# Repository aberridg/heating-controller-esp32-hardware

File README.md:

# heating-controller-esp32-hardware

This is a multi-zone heating controller, based on an ESP-32.

It uses Triacs for switching the boiler, pump and thermostats.

Right now, it is set up for 3 zones plus Domestic Hot Water.

It's designed to be used with this firmware:

https://github.com/aberridg/heating-controller-esp32-mqtt

The design can be used with physical thermostats or with triggering
via MQTT (for use with home automation systems such as Home Assistant).

[Schematic](/heating-controller-esp32.pdf)

I'm having some PCBs made/assembled by JLCPCB, so if you want one, let me know (via LinkedIn - link in my bio)! Or if you can't do that, raise an issue.

IMPORTANT: v1.0 - the connector for the thermostats is the wrong way round on the PCB, so the pin numbers are not consistent with the others. No matter, just wire accordingly. For reference, GND is the upper pin, closest to the bottom edge of the board.

Also IMPORTANT: v1.0 - to flash the ESP32, hold down the Boot button and press reset.

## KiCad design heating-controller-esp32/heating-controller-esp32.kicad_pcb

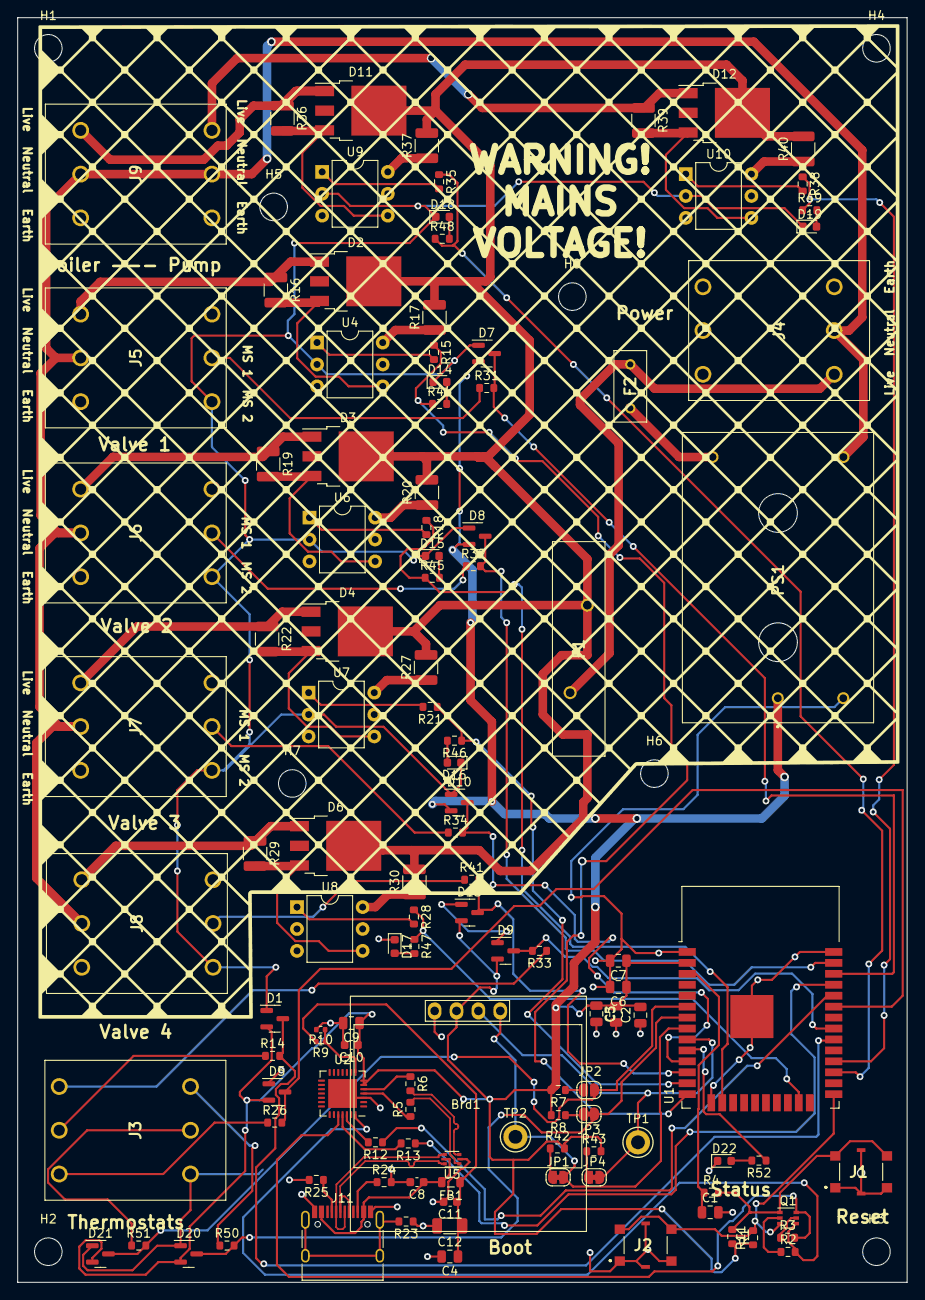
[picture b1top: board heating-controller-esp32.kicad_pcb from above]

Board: 2 copper layers, 103.3 x 146.8 mm, 125 parts (0 on the bottom side), 92 nets.

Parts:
Brd1: SSD1306; 128x64OLED
C1, C6: 1uF; C_0805_2012Metric
C2, C3, C5, C7, C9: 100nF; C_0805_2012Metric
C4: 1.0uF; C_0805_2012Metric
C8, C11: 10nF/100V; C_0603_1608Metric
C10: 4.7uF; C_0603_1608Metric
C12: 10uF; C_1206_3216Metric
D1, D5, D7, D8, D9, D10, D13, D20, D21: BAS-040; SOT-23
D2, D3, D4, D6, D11, D12: ACS2; TO-252-3_TabPin4
D14, D15, D16, D17, D18, D19, D22: RED; LED_0603_1608Metric
F1: LVR200S-240; LVR200S240
F2: MF-RM005_240-2; MFRM0052402
FB1: Ferrite_Bead; L_0805_2012Metric
H1, H2, H3, H4, H5, H6, H7, H8: MountingHole; MountingHole_3.2mm_M3_DIN965
J1, J2: 431151015826
J3, J4, J5, J6, J7, J8, J9: 76829-0104; 736303
J11: USB_C_Receptacle_USB2.0; USB_C_Receptacle_HRO_TYPE-C-31-M-12
JP1, JP4: i2cPU; SolderJumper-2_P1.3mm_Bridged_RoundedPad1.0x1.5mm
JP2: SolderJumper_2_Bridged; SolderJumper-2_P1.3mm_Open_RoundedPad1.0x1.5mm
JP3: SolderJumper_2_Bridged; SolderJumper-2_P1.3mm_Bridged_RoundedPad1.0x1.5mm
PS1: IRM-01-3.3; IRM015
Q1: MBT3904DW1; SOT-363_SC-70-6
R1: 12K; R_0603_1608Metric
R2, R3, R7, R8, R11, R42, R43: 10K; R_0603_1608Metric
R4: 22R; R_0603_1608Metric
R5, R6: 27R; R_0603_1608Metric
R9: 24K; R_0402_1005Metric
R10: 47K; R_0402_1005Metric
R12, R13: 470R; R_0603_1608Metric
R14, R26, R31, R32, R33, R34, R41, R50, R51: 4.7K; R_0603_1608Metric
R15, R18, R21, R28, R35, R38: 270R; R_0603_1608Metric
R16, R17, R19, R20, R22, R27, R29, R30, R36, R37, R39, R40: 360R; R_1210_3225Metric
R23: 1M; R_0603_1608Metric
R24, R25: 5.1K; R_0603_1608Metric
R44, R45, R46, R47, R48, R49, R52: 1K; R_0603_1608Metric
TP1, TP2: TestPoint; TestPoint_Keystone_5005-5009_Compact
U1: ESP32-WROOM-32U; ESP32-WROOM-32
U2: CP2102N-A01-GQFN28; QFN-28-1EP_5x5mm_P0.5mm_EP3.35x3.35mm
U4, U6, U7, U8, U9, U10: MOC3061M; DIP-6_W7.62mm
U5: USB ESD; SOT-666

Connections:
+3V3: Brd1.2 (VCC), C2.2, C3.1, C5.2, C6.1, C7.1, C9.1, C10.1, D1.2, D5.2, D7.2, D8.2, D9.2, D10.2, D13.2, D20.2, D21.2, PS1.1 (+V), R1.1, R7.2, R8.2, R11.1, R42.2, R43.2, U1.2 (VDD), U2.6 (VDD), U2.7 (REGIN)
/Boiler Out/Switched: D11.1 (A1), J9.1, R36.1
/Boiler Out/Trigger: R35.1, R48.1, U1.27 (IO16)
/DHW_Thermostat: J3.2, R26.1
/ESP32/DTR: Q1.4 (E2), R2.2, U2.28 (~DTR)
/ESP32/EN: C1.1, R4.1, U1.3 (EN)
/ESP32/ESP_RXD: R12.1, U1.34 (RXD0/IO3)
/ESP32/ESP_TXD: R13.1, U1.35 (TXD0/IO1)
/ESP32/GPIO_0: J2.2 (NO_1), J2.4 (NO_2), Q1.3 (C2), R11.2, U1.25 (IO0)
/ESP32/IO12: R15.1, R44.1, U1.14 (IO12)
/ESP32/IO13: R18.1, R45.1, U1.16 (IO13)
/ESP32/IO14: R21.1, R46.1, U1.13 (IO14)
/ESP32/IO15: R28.1, R47.1, U1.23 (IO15)
/ESP32/IO17: R38.1, R49.1, U1.28 (IO17)
/ESP32/IO18: D1.3, R14.2, U1.30 (IO18)
/ESP32/IO19: D9.3, R33.2, U1.31 (IO19)
/ESP32/IO21: D5.3, R26.2, U1.33 (IO21)
/ESP32/IO22: D7.3, R31.2, U1.36 (IO22)
/ESP32/IO23: D8.3, R32.2, U1.37 (IO23)
/ESP32/IO26: D10.3, R34.2, U1.11 (IO26)
/ESP32/IO27: D13.3, R41.2, U1.12 (IO27)
/ESP32/IO32: Brd1.4 (SDA), JP1.2 (B), TP2.1, U1.8 (IO32)
/ESP32/IO33: Brd1.3 (SCL), JP4.2 (B), TP1.1, U1.9 (IO33)
/ESP32/IO34: D21.3, JP2.1 (A), R51.2, U1.6 (IO34)
/ESP32/IO35: D20.3, JP3.1 (A), R50.2, U1.7 (IO35)
/ESP32/RTS: Q1.6 (C1), R3.2, U2.24 (~RTS)
/ESP32/sheet61EA3917/D+: R5.2, U5.1 (I/O1)
/ESP32/sheet61EA3917/D-: R6.2, U5.3 (I/O2)
/ESP32/sheet61EA3917/USB_D+: J11.A6 (D+), J11.B6 (D+), U5.6 (I/O1)
/ESP32/sheet61EA3917/USB_D-: J11.A7 (D-), J11.B7 (D-), U5.4 (I/O2)
/ESP32/sheet61EA3917/VBUS: C4.1, C11.1, C12.1, FB1.1, R9.1
/ESP32/~RESET: J1.2 (NO_1), J1.4 (NO_2), Q1.1 (E1), R1.2, R4.2
/Pump Out/Switched: D12.1 (A1), J9.2, R39.1
/STATUS_LED: R52.1, U1.10 (IO25)
/Spare_Thermostat: J3.4, R14.1
/Spare_Thermostat_2: J3.6, R33.1
/Spare_Thermostat_3: J3.3, R51.1
/Spare_Thermostat_4: J3.5, R50.1
/Valve Out 1/Switched: D2.1 (A1), J5.1, R16.1
/Valve Out 2/Switched: D3.1 (A1), J6.1, R19.1
/Valve Out 3/Switched: D4.1 (A1), J7.1, R22.1
/Valve Out 4/Switched: D6.1 (A1), J8.1, R29.1
/Valve_Microswitch_1: J5.4, R31.1
/Valve_Microswitch_2: J6.4, R32.1
/Valve_Microswitch_3: J7.4, R34.1
/Valve_Microswitch_4: J8.4, R41.1
Earth: J4.5, J5.5, J6.5, J7.5, J8.5, J9.5, J9.6
GND: Brd1.1 (GND), C1.2, C2.1, C3.2, C4.2, C5.1, C6.2, C7.2, C8.2, C9.2, C10.2, C11.2, C12.2, D1.1, D5.1, D7.1, D8.1, D9.1, D10.1, D13.1, D14.1 (K), D15.1 (K), D16.1 (K), D17.1 (K), D18.1 (K), D19.1 (K), D20.1, D21.1, D22.1 (K), J1.1 (COM_1), J1.3 (COM_2), J1.5 (GND_1), J1.6 (GND_2), J2.1 (COM_1), J2.3 (COM_2), J2.5 (GND_1), J2.6 (GND_2), J3.1, J5.6, J6.6, J7.6, J8.6, J11.A1 (GND), J11.A12 (GND), J11.B1 (GND), J11.B12 (GND), PS1.2 (-V), R10.2, R23.1, R24.2, R25.2, U1.1 (GND), U1.15 (GND), U1.38 (GND), U1.39 (GND), U2.3 (GND), U2.29 (GND), U4.2, U5.2 (GND), U6.2, U7.2, U8.2, U9.2, U10.2
LINE: D2.4 (A2), D3.4 (A2), D4.4 (A2), D6.4 (A2), D11.4 (A2), D12.4 (A2), F1.2, R17.2, R20.2, R27.2, R30.2, R37.2, R40.2
NEUT: J4.3, J5.3, J6.3, J7.3, J8.3, J9.3, J9.4, PS1.3 (AC/N)
unnamed: C8.1, FB1.2, J11.A4 (VBUS), J11.A9 (VBUS), J11.B4 (VBUS), J11.B9 (VBUS), U5.5 (VBUS)
unnamed: D2.3 (G), R16.2, U4.4
unnamed: D3.3 (G), R19.2, U6.4
unnamed: D4.3 (G), R22.2, U7.4
unnamed: D6.3 (G), R29.2, U8.4
unnamed: D11.3 (G), R36.2, U9.4
unnamed: D12.3 (G), R39.2, U10.4
unnamed: D14.2 (A), R44.2
unnamed: D15.2 (A), R45.2
unnamed: D16.2 (A), R46.2
unnamed: D17.2 (A), R47.2
unnamed: D18.2 (A), R48.2
unnamed: D19.2 (A), R49.2
unnamed: D22.2 (A), R52.2
unnamed: F1.1, F2.1, J4.1
unnamed: F2.2, PS1.4 (AC/L)
unnamed: J11.A5 (CC1), R25.1
unnamed: J11.B5 (CC2), R24.1
unnamed: J11.S1 (SHIELD), R23.2
unnamed: JP1.1 (A), R42.1
unnamed: JP2.2 (B), R7.1
unnamed: JP3.2 (B), R8.1
unnamed: JP4.1 (A), R43.1
unnamed: Q1.2 (B1), R2.1
unnamed: Q1.5 (B2), R3.1
unnamed: R5.1, U2.4 (D+)
unnamed: R6.1, U2.5 (D-)
unnamed: R9.2, R10.1, U2.8 (VBUS)
unnamed: R12.2, U2.26 (TXD)
unnamed: R13.2, U2.25 (RXD)
unnamed: R15.2, U4.1
unnamed: R17.1, U4.6
unnamed: R18.2, U6.1
unnamed: R20.1, U6.6
unnamed: R21.2, U7.1
unnamed: R27.1, U7.6
unnamed: R28.2, U8.1
unnamed: R30.1, U8.6
unnamed: R35.2, U9.1
unnamed: R37.1, U9.6
unnamed: R38.2, U10.1
unnamed: R40.1, U10.6

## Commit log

2022-06-09 First commit of initial schematic design
2022-06-10 Initial design of schematic complete. Started laying out PCB
2022-06-11 Changed to Wago connectors; initial routing completed
2022-06-11 Minor tweaks
2022-06-11 Added additional spare thermostat inputs
2022-06-11 Mounting holes, a few more tweaks
2022-06-11 Fabrication outputs
2022-06-11 Oops. Missing certain files for commit.
2022-06-11 Bringing in step with the other files
2022-06-11 Changes for JLCB fabrication using https://github.com/Bouni/kicad-jlcpcb-tools
2022-06-11 Minor updates and update of README.md
2022-06-11 Added schematic pdf
2022-06-12 Current limiting resistors for MOC devices changed to 0.5W
2022-06-13 Assign netclasses (should have done this earlier)! Small tweaks; status LED added.
2022-06-13 Ordered from JLCPCB.com as version 1.0
2022-06-17 Not 100% sure what I did, but committing to keep in step with what's on my computer. Probably still v1.0
2022-06-26 Added note about the connector for thermostats being the wrong way round on the PCB
